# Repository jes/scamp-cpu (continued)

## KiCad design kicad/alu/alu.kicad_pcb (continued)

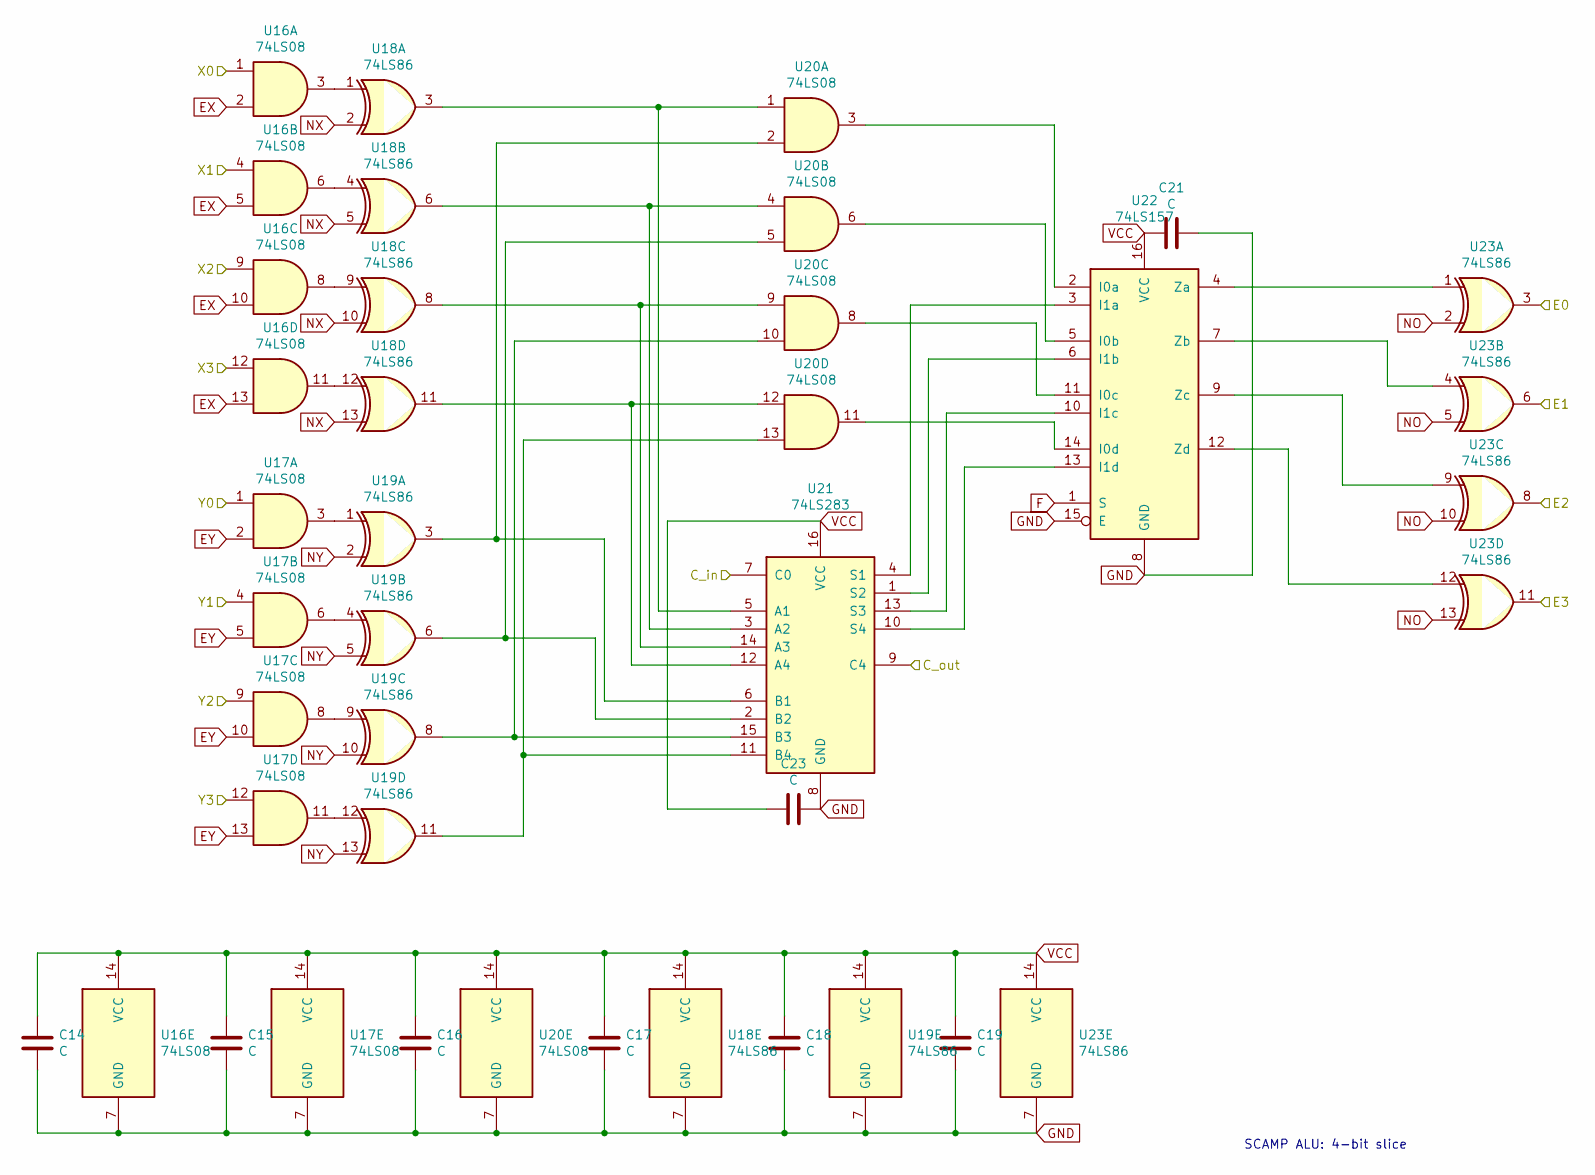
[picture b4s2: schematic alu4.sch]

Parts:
C14, C15, C16, C17, C18, C19, C20, C22: C; C_Disc_D5.0mm_W2.5mm_P2.50mm
U7, U8, U9: 74LS08; DIP-14_W7.62mm_Socket
U11: 74LS283; DIP-16_W7.62mm_Socket
U12: 74LS157; DIP-16_W7.62mm_Socket
U13, U14, U15: 74LS86; DIP-14_W7.62mm_Socket

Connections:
/aluhigh/C_in: U11.9 (C4); also elsewhere on the board
E0: U15.3; also elsewhere on the board
E1: U15.6; also elsewhere on the board
E2: U15.8; also elsewhere on the board
E3: U15.11; also elsewhere on the board
EX: U7.2, U7.5, U7.10, U7.13; also elsewhere on the board
EY: U8.2, U8.5, U8.10, U8.13; also elsewhere on the board
F: U12.1 (S); also elsewhere on the board
GND: C14.2, C15.2, C16.2, C17.2, C18.2, C19.2, C20.1, C22.1, U7.7 (GND), U8.7 (GND), U9.7 (GND), U11.8 (GND), U12.8 (GND), U12.15 (E), U13.7 (GND), U14.7 (GND), U15.7 (GND); also elsewhere on the board
NO: U15.2, U15.5, U15.10, U15.13; also elsewhere on the board
NX: U13.2, U13.5, U13.10, U13.13; also elsewhere on the board
NY: U14.2, U14.5, U14.10, U14.13; also elsewhere on the board
unnamed: U11.1 (S2), U12.6 (I1b)
unnamed: U9.5, U11.2 (B2), U14.6
unnamed: U9.4, U11.3 (A2), U13.6
unnamed: U11.4 (S1), U12.3 (I1a)
unnamed: U9.1, U11.5 (A1), U13.3
unnamed: U9.2, U11.6 (B1), U14.3
unnamed: U11.10 (S4), U12.13 (I1d)
unnamed: U9.13, U11.11 (B4), U14.11
unnamed: U9.12, U11.12 (A4), U13.11
unnamed: U11.13 (S3), U12.10 (I1c)
unnamed: U9.9, U11.14 (A3), U13.8
unnamed: U9.10, U11.15 (B3), U14.8
unnamed: U9.3, U12.2 (I0a)
unnamed: U12.4 (Za), U15.1
unnamed: U9.6, U12.5 (I0b)
unnamed: U12.7 (Zb), U15.4
unnamed: U12.9 (Zc), U15.9
unnamed: U9.8, U12.11 (I0c)
unnamed: U12.12 (Zd), U15.12
unnamed: U9.11, U12.14 (I0d)
unnamed: U7.3, U13.1
unnamed: U7.6, U13.4
unnamed: U7.8, U13.9
unnamed: U7.11, U13.12
unnamed: U8.3, U14.1
unnamed: U8.6, U14.4
unnamed: U8.8, U14.9
unnamed: U8.11, U14.12
VCC: C14.1, C15.1, C16.1, C17.1, C18.1, C19.1, C20.2, C22.2, U7.14 (VCC), U8.14 (VCC), U9.14 (VCC), U11.16 (VCC), U12.16 (VCC), U13.14 (VCC), U14.14 (VCC), U15.14 (VCC); also elsewhere on the board
X0: U7.1; also elsewhere on the board
X1: U7.4; also elsewhere on the board
X2: U7.9; also elsewhere on the board
X3: U7.12; also elsewhere on the board
Y0: U8.1; also elsewhere on the board
Y1: U8.4; also elsewhere on the board
Y2: U8.9; also elsewhere on the board
Y3: U8.12; also elsewhere on the board
carry_in: U11.7 (C0); also elsewhere on the board

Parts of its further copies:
C8, C9, C10, C11, C12, C13, C21, C23: C; C_Disc_D5.0mm_W2.5mm_P2.50mm
U18, U19, U23: 74LS86; DIP-14_W7.62mm_Socket
U20: 74LS08; DIP-14_W7.62mm_Socket
U21: 74LS283; DIP-16_W7.62mm_Socket
U22: 74LS157; DIP-16_W7.62mm_Socket

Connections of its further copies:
/aluhigh/C_in: U21.7 (C0); also elsewhere on the board
E4: U23.3; also elsewhere on the board
E5: U23.6; also elsewhere on the board
E6: U23.8; also elsewhere on the board
E7: U23.11; also elsewhere on the board
F: U22.1 (S); also elsewhere on the board
GND: C8.2, C9.2, C10.2, C11.2, C12.2, C13.2, C21.1, C23.1, U18.7 (GND), U19.7 (GND), U20.7 (GND), U21.8 (GND), U22.8 (GND), U22.15 (E), U23.7 (GND); also elsewhere on the board
NO: U23.2, U23.5, U23.10, U23.13; also elsewhere on the board
NX: U18.2, U18.5, U18.10, U18.13; also elsewhere on the board
NY: U19.2, U19.5, U19.10, U19.13; also elsewhere on the board
unnamed 144: U18.1; also elsewhere on the board
unnamed 145: U18.4; also elsewhere on the board
unnamed 146: U18.9; also elsewhere on the board
unnamed 147: U18.12; also elsewhere on the board
unnamed 148: U19.1; also elsewhere on the board
unnamed 149: U19.4; also elsewhere on the board
unnamed 150: U19.9; also elsewhere on the board
unnamed 151: U19.12; also elsewhere on the board
unnamed: U18.3, U20.1, U21.5 (A1)
unnamed: U18.6, U20.4, U21.3 (A2)
unnamed: U18.8, U20.9, U21.14 (A3)
unnamed: U18.11, U20.12, U21.12 (A4)
unnamed: U19.3, U20.2, U21.6 (B1)
unnamed: U19.6, U20.5, U21.2 (B2)
unnamed: U19.8, U20.10, U21.15 (B3)
unnamed: U19.11, U20.13, U21.11 (B4)
unnamed: U20.3, U22.2 (I0a)
unnamed: U20.6, U22.5 (I0b)
unnamed: U20.8, U22.11 (I0c)
unnamed: U20.11, U22.14 (I0d)
unnamed: U21.1 (S2), U22.6 (I1b)
unnamed: U21.4 (S1), U22.3 (I1a)
unnamed: U21.10 (S4), U22.13 (I1d)
unnamed: U21.13 (S3), U22.10 (I1c)
unnamed: U22.4 (Za), U23.1
unnamed: U22.7 (Zb), U23.4
unnamed: U22.9 (Zc), U23.9
unnamed: U22.12 (Zd), U23.12
VCC: C8.1, C9.1, C10.1, C11.1, C12.1, C13.1, C21.2, C23.2, U18.14 (VCC), U19.14 (VCC), U20.14 (VCC), U21.16 (VCC), U22.16 (VCC), U23.14 (VCC); also elsewhere on the board
carry_out: U21.9 (C4); also elsewhere on the board

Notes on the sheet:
SCAMP ALU: 4-bit slice

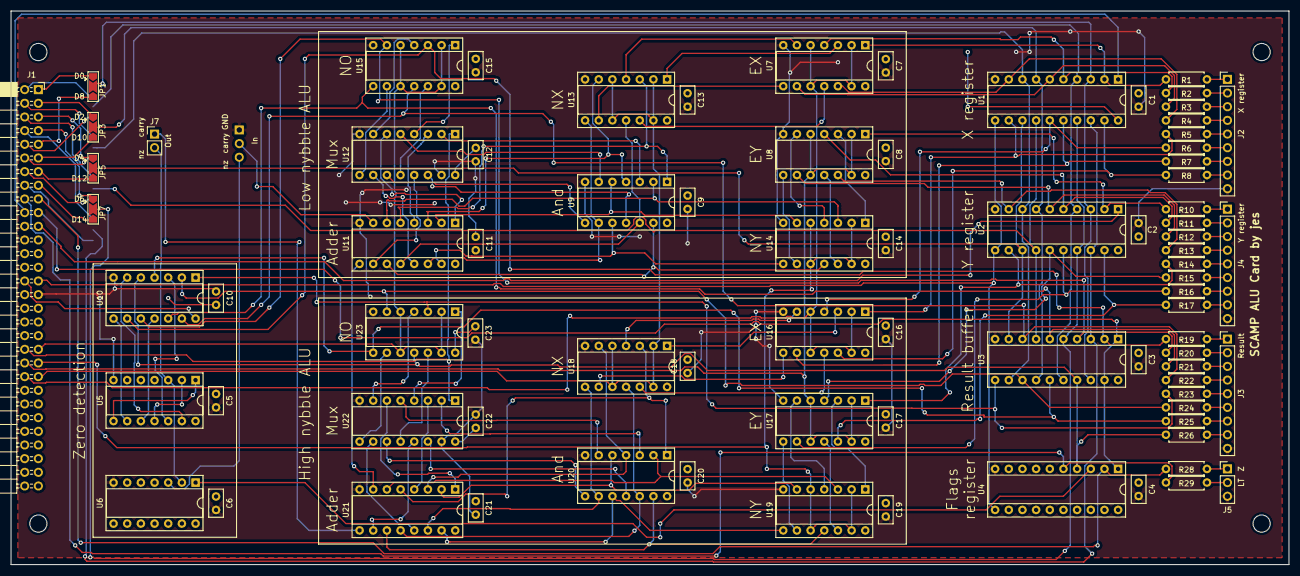
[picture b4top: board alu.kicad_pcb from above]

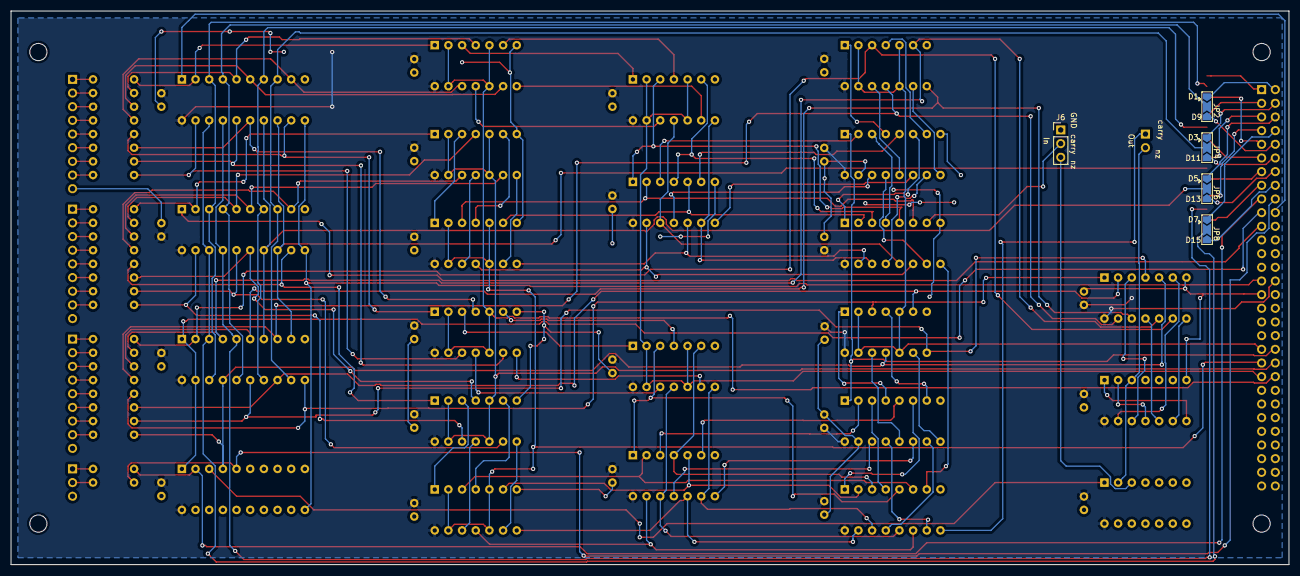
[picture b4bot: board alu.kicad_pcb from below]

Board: 2 copper layers, 237.5 x 102.9 mm, 87 parts (5 on the bottom side), 156 nets.

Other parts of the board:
U16, U17: 74LS08; DIP-14_W7.62mm_Socket

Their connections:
EX: U16.2, U16.5, U16.10, U16.13; also elsewhere on the board
EY: U17.2, U17.5, U17.10, U17.13; also elsewhere on the board
GND: U16.7, U17.7; also elsewhere on the board
unnamed 144: U16.3; also elsewhere on the board
unnamed 145: U16.6; also elsewhere on the board
unnamed 146: U16.8; also elsewhere on the board
unnamed 147: U16.11; also elsewhere on the board
unnamed 148: U17.3; also elsewhere on the board
unnamed 149: U17.6; also elsewhere on the board
unnamed 150: U17.8; also elsewhere on the board
unnamed 151: U17.11; also elsewhere on the board
VCC: U16.14, U17.14; also elsewhere on the board
X4: U16.1; also elsewhere on the board
X5: U16.4; also elsewhere on the board
X6: U16.9; also elsewhere on the board
X7: U16.12; also elsewhere on the board
Y4: U17.1; also elsewhere on the board
Y5: U17.4; also elsewhere on the board
Y6: U17.9; also elsewhere on the board
Y7: U17.12; also elsewhere on the board

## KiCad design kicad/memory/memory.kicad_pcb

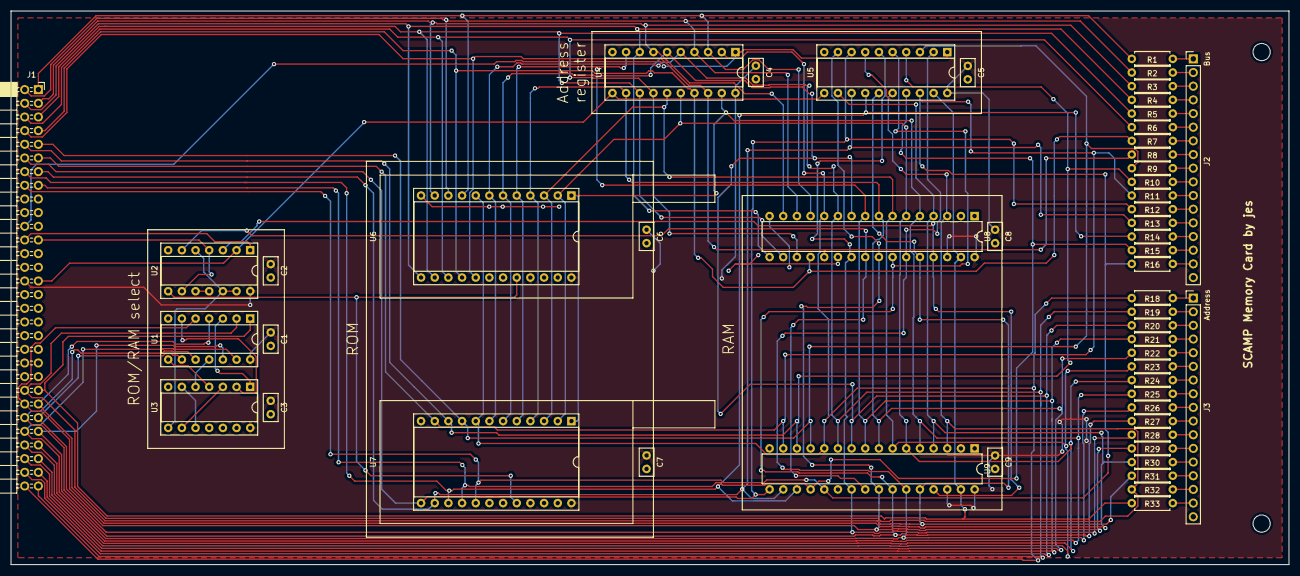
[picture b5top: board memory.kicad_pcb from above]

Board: 2 copper layers, 237.5 x 102.9 mm, 53 parts (0 on the bottom side), 81 nets.

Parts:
C1, C2, C3, C4, C5, C6, C7, C8, C9: C; C_Disc_D5.0mm_W2.5mm_P2.50mm
J1: Conn_02x30_Counter_Clockwise; PinSocket_2x30_P2.54mm_Horizontal
J2, J3: Conn_01x17_Male; PinHeader_1x17_P2.54mm_Vertical
R1, R2, R3, R4, R5, R6, R7, R8, R9, R10, R11, R12, R13, R14, R15, R16, R18, R19, R20, R21, R22, R23, R24, R25, R26, R27, R28, R29, R30, R31, R32, R33: R; R_Axial_DIN0207_L6.3mm_D2.5mm_P7.62mm_Horizontal
U1, U3: 74LS32; DIP-14_W7.62mm_Socket
U2: 74LS00; DIP-14_W7.62mm_Socket
U4, U5: 74LS377; DIP-20_W7.62mm_Socket
U6, U7: 28C16; DIP-24_W15.24mm_Socket
U8, U9: W24512A; DIP-32_W7.62mm

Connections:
A0: J1.60, R18.1, U4.2, U6.8, U7.8, U8.12, U9.12
A1: J1.59, R19.1, U4.5, U6.7, U7.7, U8.11, U9.11
A2: J1.58, R20.1, U4.6, U6.6, U7.6, U8.10, U9.10
A3: J1.57, R21.1, U4.9, U6.5, U7.5, U8.9, U9.9
A4: J1.56, R22.1, U4.12, U6.4, U7.4, U8.8, U9.8
A5: J1.55, R23.1, U4.15, U6.3, U7.3, U8.7, U9.7
A6: J1.54, R24.1, U4.16, U6.2, U7.2, U8.6, U9.6
A7: J1.53, R25.1, U4.19, U6.1, U7.1, U8.5, U9.5
A8: J1.52, R26.1, U1.13, U5.2, U8.27, U9.27
A9: J1.51, R27.1, U1.12, U5.5, U8.26, U9.26
A10: J1.50, R28.1, U1.10, U5.6, U8.23, U9.23
A11: J1.49, R29.1, U1.9, U5.9, U8.25, U9.25
A12: J1.48, R30.1, U1.5, U5.12, U8.4, U9.4
A13: J1.47, R31.1, U1.4, U5.15, U8.28, U9.28
A14: J1.46, R32.1, U1.2, U5.16, U8.3, U9.3
A15: J1.45, R33.1, U1.1, U5.19, U8.31, U9.31
CLK: J1.29, U2.2, U4.11, U5.11
D0: J1.1, R1.1, U4.3, U6.9, U8.13
D1: J1.2, R2.1, U4.4, U6.10, U8.14
D2: J1.3, R3.1, U4.7, U6.11, U8.15
D3: J1.4, R4.1, U4.8, U6.13, U8.17
D4: J1.5, R5.1, U4.13, U6.14, U8.18
D5: J1.6, R6.1, U4.14, U6.15, U8.19
D6: J1.7, R7.1, U4.17, U6.16, U8.20
D7: J1.8, R8.1, U4.18, U6.17, U8.21
D8: J1.9, R9.1, U5.3, U7.9, U9.13
D9: J1.10, R10.1, U5.4, U7.10, U9.14
D10: J1.11, R11.1, U5.7, U7.11, U9.15
D11: J1.12, R12.1, U5.8, U7.13, U9.17
D12: J1.13, R13.1, U5.13, U7.14, U9.18
D13: J1.14, R14.1, U5.14, U7.15, U9.19
D14: J1.15, R15.1, U5.17, U7.16, U9.20
D15: J1.16, R16.1, U5.18, U7.17, U9.21
GND: C1.2, C2.2, C3.2, C4.2, C5.2, C6.2, C7.2, C8.2, C9.2, J1.31, J2.17, J3.17, U1.7, U2.7, U3.7, U4.10, U5.10, U6.12, U6.18, U6.19, U6.22, U6.23, U7.12, U7.18, U7.19, U7.22, U7.23, U8.16, U8.22, U9.16, U9.22
MI: J1.24, U2.1
MO: J1.23, U2.4, U2.9
unnamed: J2.1, R1.2
unnamed: J2.2, R2.2
unnamed: J2.3, R3.2
unnamed: J2.4, R4.2
unnamed: J2.5, R5.2
unnamed: J2.6, R6.2
unnamed: J2.7, R7.2
unnamed: J2.8, R8.2
unnamed: J2.9, R9.2
unnamed: J2.10, R10.2
unnamed: J2.11, R11.2
unnamed: J2.12, R12.2
unnamed: J2.13, R13.2
unnamed: J2.14, R14.2
unnamed: J2.15, R15.2
unnamed: J2.16, R16.2
unnamed: J3.1, R18.2
unnamed: J3.2, R19.2
unnamed: J3.3, R20.2
unnamed: J3.4, R21.2
unnamed: J3.5, R22.2
unnamed: J3.6, R23.2
unnamed: J3.7, R24.2
unnamed: J3.8, R25.2
unnamed: J3.9, R26.2
unnamed: J3.10, R27.2
unnamed: J3.11, R28.2
unnamed: J3.12, R29.2
unnamed: J3.13, R30.2
unnamed: J3.14, R31.2
unnamed: J3.15, R32.2
unnamed: J3.16, R33.2
unnamed: U1.3, U3.1
unnamed: U1.6, U3.2
unnamed: U1.8, U3.4
unnamed: U1.11, U3.5
unnamed: U2.10, U2.11
unnamed: U3.3, U3.9
unnamed: U3.6, U3.10
VCC: C1.1, C2.1, C3.1, C4.1, C5.1, C6.1, C7.1, C8.1, C9.1, J1.30, U1.14, U2.14, U3.14, U4.20, U5.20, U6.21, U6.24, U7.21, U7.24, U8.30, U8.32, U9.30, U9.32
want_ram: U2.5, U2.12, U2.13, U3.8
~AI~: J1.22, U4.1, U5.1
~LOAD_CLK~: U2.3, U8.29, U9.29
~RAM_EN~: U2.6, U8.24, U9.24
~ROM_EN~: U2.8, U6.20, U7.20

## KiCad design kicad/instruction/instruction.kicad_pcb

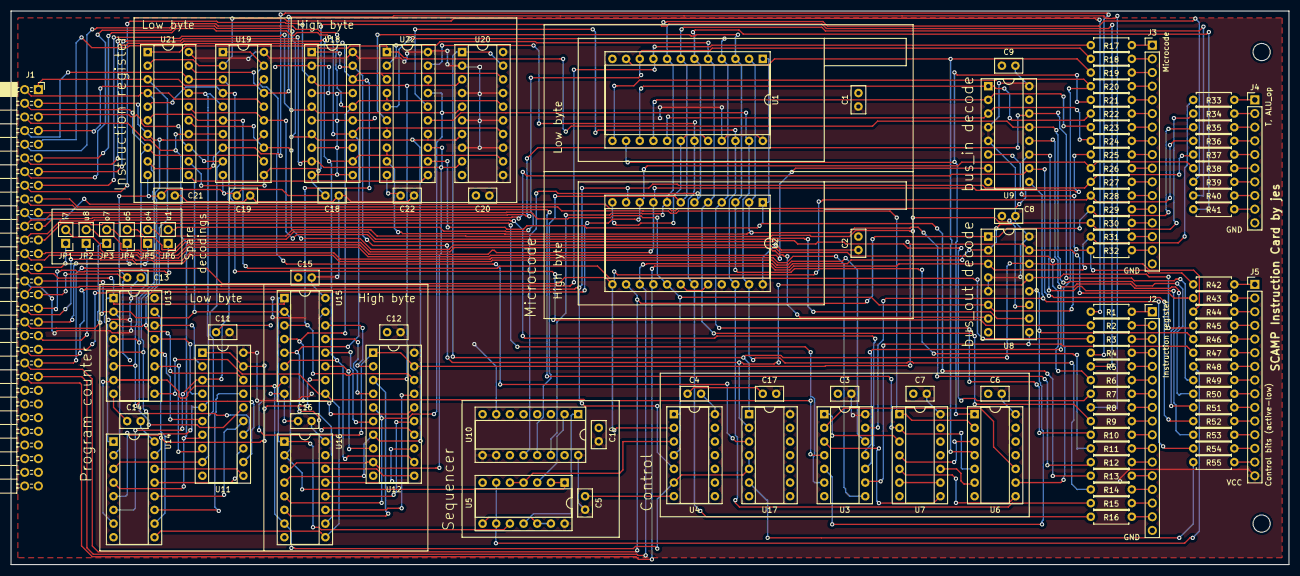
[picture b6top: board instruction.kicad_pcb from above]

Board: 2 copper layers, 237.5 x 102.9 mm, 110 parts (0 on the bottom side), 172 nets.

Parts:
C1, C2, C3, C4, C5, C6, C7, C8, C9, C10, C11, C12, C13, C14, C15, C16, C17, C18, C19, C20, C21, C22: C; C_Disc_D5.0mm_W2.5mm_P2.50mm
J1: Conn_02x30_Counter_Clockwise; PinSocket_2x30_P2.54mm_Horizontal
J2, J3: Conn_01x17_Male; PinHeader_1x17_P2.54mm_Vertical
J4: Conn_01x10_Male; PinHeader_1x10_P2.54mm_Vertical
J5: Conn_01x15_Male; PinHeader_1x15_P2.54mm_Vertical
JP1, JP2, JP3, JP4, JP5, JP6: Jumper_NO_Small; PinHeader_1x02_P2.54mm_Vertical
R1, R2, R3, R4, R5, R6, R7, R8, R9, R10, R11, R12, R13, R14, R15, R16, R17, R18, R19, R20, R21, R22, R23, R24, R25, R26, R27, R28, R29, R30, R31, R32, R33, R34, R35, R36, R37, R38, R39, R40, R41, R42, R43, R44, R45, R46, R47, R48, R49, R50, R51, R52, R53, R54, R55: R; R_Axial_DIN0207_L6.3mm_D2.5mm_P7.62mm_Horizontal
U1, U2: 28C16; DIP-24_W15.24mm_Socket
U3: 74LS04; DIP-14_W7.62mm_Socket
U4, U6: 74LS08; DIP-14_W7.62mm_Socket
U5, U17: 74LS00; DIP-14_W7.62mm_Socket
U7: 74LS32; DIP-14_W7.62mm_Socket
U8, U9: 74LS138; DIP-16_W7.62mm_Socket
U10, U13, U14, U15, U16: 74LS161; DIP-16_W7.62mm_Socket
U11, U12, U18, U19, U20: 74LS244; DIP-20_W7.62mm_Socket
U21, U22: 74LS377; DIP-20_W7.62mm_Socket

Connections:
CLK: J1.29, U5.1, U5.2, U13.2, U14.2, U15.2, U16.2, U21.11, U22.11
D0: J1.1, U11.18, U13.3, U19.18, U21.3
D1: J1.2, U11.16, U13.4, U19.16, U21.4
D2: J1.3, U11.14, U13.5, U19.14, U21.7
D3: J1.4, U11.12, U13.6, U19.12, U21.8
D4: J1.5, U11.9, U14.3, U19.9, U21.13
D5: J1.6, U11.7, U14.4, U19.7, U21.14
D6: J1.7, U11.5, U14.5, U19.5, U21.17
D7: J1.8, U11.3, U14.6, U19.3, U21.18
D8: J1.9, U12.18, U15.3, U18.18, U20.18, U22.3
D9: J1.10, U12.16, U15.4, U18.16, U20.16, U22.4
D10: J1.11, U12.14, U15.5, U18.14, U20.14, U22.7
D11: J1.12, U12.12, U15.6, U18.12, U20.12, U22.8
D12: J1.13, U12.9, U16.3, U18.9, U20.9, U22.13
D13: J1.14, U12.7, U16.4, U18.7, U20.7, U22.14
D14: J1.15, U12.5, U16.5, U18.5, U20.5, U22.17
D15: J1.16, U12.3, U16.6, U18.3, U20.3, U22.18
DI: J1.26, U3.12
DO: J1.25, U3.8
EX: J1.44, R31.1, R33.1, U2.16, U8.3
EY: J1.42, R29.1, R35.1, U2.14, U8.1
F: J1.40, R27.1, R37.1, U2.11, U4.5
GND: C1.2, C2.2, C3.2, C4.2, C5.2, C6.2, C7.2, C8.2, C9.2, C10.2, C11.2, C12.2, C13.2, C14.2, C15.2, C16.2, C17.2, C18.2, C19.2, C20.2, C21.2, C22.2, J1.31, J2.17, J3.17, J4.10, U1.12, U1.18, U1.20, U2.12, U2.18, U2.20, U3.7, U4.7, U5.7, U6.7, U7.7, U8.8, U9.8, U10.8, U11.10, U12.10, U13.8, U14.8, U15.8, U16.8, U17.7, U18.2, U18.4, U18.6, U18.8, U18.10, U18.11, U18.13, U18.15, U18.17, U19.10, U20.10, U21.10, U22.10
GT: U3.2, U6.10
I0: R1.1, U19.2, U21.2
I1: R2.1, U19.4, U21.5
I2: R3.1, U19.6, U21.6
I3: R4.1, U19.8, U21.9
I4: R5.1, U19.11, U21.12
I5: R6.1, U19.13, U21.15
I6: R7.1, U19.15, U21.16
I7: R8.1, U19.17, U21.19
I8: R9.1, U1.5, U2.5, U22.2
I9: R10.1, U1.4, U2.4, U22.5
I10: R11.1, U1.3, U2.3, U22.6
I11: R12.1, U1.2, U2.2, U22.9
I12: R13.1, U1.1, U2.1, U22.12
I13: R14.1, U1.23, U2.23, U22.15
I14: R15.1, U1.22, U2.22, U22.16
I15: R16.1, U1.19, U2.19, U22.19
JGT: R20.1, U1.13, U6.9
JGT_GT: U6.8, U7.5
JLT: R19.1, U1.11, U6.4
JLT_LT: U6.6, U7.10
JMP: U3.3, U7.8
JZ: R21.1, U1.14, U6.1
JZ_Z: U6.3, U7.4
LT: J1.18, U6.5, U7.2
MI: J1.24, U3.10
MO: J1.23, U3.6
NO: J1.39, R26.1, R38.1, U2.10
NX: J1.43, R30.1, R34.1, U2.15, U8.2
NY: J1.41, R28.1, R36.1, U2.13, U4.2
unnamed: J1.27, JP1.1
unnamed: J1.33, JP6.1
unnamed: J1.34, JP5.1
unnamed: J1.35, JP4.1
unnamed: J1.36, JP3.1
unnamed: J1.37, JP2.1
unnamed: J2.1, R1.2
unnamed: J2.2, R2.2
unnamed: J2.3, R3.2
unnamed: J2.4, R4.2
unnamed: J2.5, R5.2
unnamed: J2.6, R6.2
unnamed: J2.7, R7.2
unnamed: J2.8, R8.2
unnamed: J2.9, R9.2
unnamed: J2.10, R10.2
unnamed: J2.11, R11.2
unnamed: J2.12, R12.2
unnamed: J2.13, R13.2
unnamed: J2.14, R14.2
unnamed: J2.15, R15.2
unnamed: J2.16, R16.2
unnamed: J3.1, R17.2
unnamed: J3.2, R18.2
unnamed: J3.3, R19.2
unnamed: J3.4, R20.2
unnamed: J3.5, R21.2
unnamed: J3.6, R22.2
unnamed: J3.7, R23.2
unnamed: J3.8, R24.2
unnamed: J3.9, R25.2
unnamed: J3.10, R26.2
unnamed: J3.11, R27.2
unnamed: J3.12, R28.2
unnamed: J3.13, R29.2
unnamed: J3.14, R30.2
unnamed: J3.15, R31.2
unnamed: J3.16, R32.2
unnamed: J4.1, R33.2
unnamed: J4.2, R34.2
unnamed: J4.3, R35.2
unnamed: J4.4, R36.2
unnamed: J4.5, R37.2
unnamed: J4.6, R38.2
unnamed: J4.7, R39.2
unnamed: J4.8, R40.2
unnamed: J4.9, R41.2
unnamed: J5.1, R42.2
unnamed: J5.2, R43.2
unnamed: J5.3, R44.2
unnamed: J5.4, R45.2
unnamed: J5.5, R46.2
unnamed: J5.6, R47.2
unnamed: J5.7, R48.2
unnamed: J5.8, R49.2
unnamed: J5.9, R50.2
unnamed: J5.10, R51.2
unnamed: J5.11, R52.2
unnamed: J5.12, R53.2
unnamed: J5.13, R54.2
unnamed: J5.14, R55.2
unnamed: U5.8, U5.12, U5.13
unnamed: U7.6, U7.9
unnamed: U13.15, U14.10
unnamed: U14.15, U15.10
unnamed: U15.15, U16.10
P0: U11.2, U13.14
P1: U11.4, U13.13
P2: U11.6, U13.12
P3: U11.8, U13.11
P4: U11.11, U14.14
P5: U11.13, U14.13
P6: U11.15, U14.12
P7: U11.17, U14.11
P8: U12.2, U15.14
P9: U12.4, U15.13
P10: U12.6, U15.12
P11: U12.8, U15.11
P12: U12.11, U16.14
P13: U12.13, U16.13
P14: U12.15, U16.12
P15: U12.17, U16.11
PP: U4.6, U13.7, U13.10, U14.7, U15.7, U16.7, U17.4, U17.5
RT: U4.3, U5.4, U5.5
T0: R39.1, U1.8, U2.8, U10.14
T1: R40.1, U1.7, U2.7, U10.13
T2: R41.1, U1.6, U2.6, U10.12
U0: J1.32, R17.1, U1.9
U1: JP6.2, R18.1, U1.10
U5: R22.1, U1.15, U9.1
U6: R23.1, U1.16, U9.2
U7: R24.1, U1.17, U9.3
U8: JP2.2, R25.1, U2.9
U15: J1.19, R32.1, R42.1, U2.17, U4.1, U4.4, U8.6, U9.6
VCC: C1.1, C2.1, C3.1, C4.1, C5.1, C6.1, C7.1, C8.1, C9.1, C10.1, C11.1, C12.1, C13.1, C14.1, C15.1, C16.1, C17.1, C18.1, C19.1, C20.1, C21.1, C22.1, J1.30, J5.15, U1.21, U1.24, U2.21, U2.24, U3.14, U4.14, U5.14, U6.14, U7.14, U8.4, U8.5, U8.16, U9.4, U9.5, U9.16, U10.7, U10.9, U10.10, U10.16, U11.20, U12.20, U13.16, U14.16, U15.16, U16.16, U17.14, U18.20, U19.20, U20.2, U20.4, U20.6, U20.8, U20.11, U20.13, U20.15, U20.17, U20.20, U21.20, U22.20
Z: J1.17, U6.2, U7.1
Z_LT: U3.1, U7.3
inv_CLK: U5.3, U10.2
inv_DI: R54.1, U3.13, U9.9
inv_DO: R47.1, U3.9, U8.9
inv_MI: R53.1, U3.11, U9.12
inv_MO: R46.1, U3.5, U8.12
inv_PP: R55.1, U17.6
inv_RT: R48.1, U5.6, U5.9
spare_I7: JP1.2, U9.7
spare_O4: JP5.2, U8.11
spare_O5: JP4.2, U8.10
spare_O7: JP3.2, U8.7
~AI~: J1.22, R49.1, U9.14
~II~: R50.1, U9.13, U21.1, U22.1
~IOH~: R44.1, U8.14, U17.1, U20.1, U20.19
~IOLH~: U17.3, U19.1, U19.19
~IOL~: R45.1, U8.13, U17.2, U18.1, U18.19
~JMP~: U3.4, U13.9, U14.9, U15.9, U16.9
~PO~: R43.1, U8.15, U11.1, U11.19, U12.1, U12.19
~RESET~: J1.28, U5.10, U13.1, U14.1, U15.1, U16.1
~XI~: J1.20, R51.1, U9.11
~YI~: J1.21, R52.1, U9.10
~reset_T~: U5.11, U10.1

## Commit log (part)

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2021-11-20 Add SER_LONGREAD flag
2021-11-20 serial: make use of LONGREAD flag, and delayed packet ACK, to improve throughput
2021-11-20 Revert "aocproxy: recover from unexpected response, and run slow enough for real hardware"
    This reverts commit 062cfcdbba21daf2abf59ec83e97bf648681db07.
2021-11-20 Revert "Update serial protocol to support checksums and synchronisation"
    This reverts commit d104ef9712ae535607cd63ff953dd1113420b1ce.
2021-11-20 Add more serial protocol documentation
2021-11-20 aoc: buffer in memory instead of writing to stdout
2021-11-20 aoc: show content on stderr while buffering
2021-11-22 kilo: show 'finding ...' while finding
2021-11-22 glob: don't let '*' match a leading '.'
2021-11-22 Add ps
2021-11-22 ps: close fd after reading
2021-11-22 slc: don't check args[1] if args[0] isn't set
2021-11-22 aoc: don't print uninitialised strings for empty data
2021-11-22 peepopt: optimise another 'ld x, foo; call x' case
2021-11-22 Mention that work has started on 'const' supported
2021-11-26 serial: only enable cooked mode by default for the console, not all devices
2021-11-26 SCAMP::Serial: make clearer when it's ready
2021-11-26 Increase serial transfer speed by 10% (any more becomes unreliable)
2021-11-28 ser: buffer in memory
2021-11-29 kernel: don't crash when restoring a large program into memory
    The problem was that in the event that you ask read() for more than 254 words,
    and the current pointer is at the start of a block on disk, read() will ask cf_blkread()
    to read directly into the user buffer, rather than memcpy()ing to it.
    The problem is that if the program we're restoring is very large, this can lead to
    cf_blkread() putting 254 words into memory, even when the remaining words in the file
    is lower than that, which overwrites some of the kernel causing a crash.
2021-12-01 atoi: move to asm, 2x faster
2021-12-01 install: sudo
2021-12-01 Unlicense
2021-12-02 Link to James Sharman
2021-12-03 aoc: don't show output twice on 'submit'
2021-12-03 Add assert()
2021-12-03 wc: accept a filename on the command line
2021-12-03 Put a trailing newline on submission results
2021-12-03 kilo: make paging behaviour more useful
2021-12-03 Remove unused files from compiler/
2021-12-05 slangc: don't warn about locals overriding globals
2021-12-06 kilo: increase horizontal scroll step size
2021-12-06 init: clear out /tmp,/proc, and save context switching to cat
2021-12-06 Add link to Advent of Code solutions
2021-12-06 Add new picture of computer
2021-12-06 kilo: don't scroll the top line off the help page
2021-12-06 Plan to support more fds
2021-12-06 Add swap()
2021-12-06 serial: fix callback function signature
2021-12-06 aocproxy: add way to get only part 2 without re-sending part 1
2021-12-07 sh: make die() non-fatal
2021-12-11 head: use setbuf
2021-12-11 kilo: add >,< shortcuts for indenting with tab
2021-12-13 Set bs=1k on install script
2021-12-15 Add vzmalloc,vfree
2021-12-15 vfree: free the intermediate arrays
2021-12-15 bufio: fix pseudocode
2021-12-15 asm: don't unlink the output of the 1st pass
2021-12-16 init: don't clear out /tmp
2021-12-27 cf: pre-increment instead of post-increment, to save 1 cycle per IO instruction
2021-12-27 memcpy: pre-increment instead of post-increment, to save 2 cycles per word copied
2021-12-27 Document new instructions
2021-12-29 slangc: turn off recursion warnings
2021-12-29 Peephole optimise new y register usage; remove nand and nor instructions
2022-01-04 atoibase: use atoi when base==10
2022-01-04 bputs: into asm
2022-01-04 Minor improvement to AnyChar
2022-01-28 asm: bodge to allow hashes in .str
2022-05-11 Use lt instead of < in utoabase()
2022-06-12 Add savetpa() syscall
2022-06-13 Add missing endline
2022-06-13 bgetc: make it possible to distinguish between a 0xffff character and EOF condition
2022-06-15 Document bug
2022-06-18 Plan to cache compiled binary in rude
2022-06-19 More efficient format for passing bulk externs into slangc
2022-06-19 Use externs list instead of lib.h/lib.s in slc (knocks ~10s off compile times)
2022-06-19 Asm undirent()
2022-06-19 slangc: support passing foot asm on command line
2022-06-19 Prefer puts() over printf()
2022-06-19 fprintf -> fputs
2022-06-19 bprintf->bput[cs]: save ~1s
2022-06-20 write(): save wasting time on memcpy() and blkread()
    I'm not completely sure that the idea of using cf_blkread_head() is
    legit. If this doesn't work on real hardware then that part will need
    to be reverted.
2022-06-20 kernel: don't truncate or unlink proc files, saves lots of time
2022-06-20 Fix ucode for 'ld (x), i16'
    It was actually implementing 'ld ((x)), i16'
2022-06-20 No longer need to writeglobalsfile() in compile()
2022-06-21 asm implementation of htmaybegrow()
2022-06-21 Fix strlen() of empty string
2022-06-21 Slightly better bgetc()
2022-06-21 Slightly better hashstr()
2022-06-21 Fix fd leak
2022-06-21 Add getpid() syscall
2022-06-21 RUDE: Implement kilo()
2022-06-23 exit(0) after running entrypoint
2022-06-23 RUDE: write out initial stack pointer every time
2022-06-23 Store source of defined functions, allow reversion
2022-06-24 rude: don't strdup all the globals with static strings
2022-06-24 Remove malloc spam
2022-06-24 rude: implement list()
2022-06-26 slangc: add 'gullible' mode where externs aren't validated
2022-06-26 rude: set return value for non-function-call statements
2022-06-27 Revert "rude: set return value for non-function-call statements"
    This reverts commit a1a440ccd0cbc6f2ab523a9250f99b07b84c3dda.
    Functions aren't required to leave their return value in x, so calling
    functions written in assembly language might not work, so we'll just
    put it back to how it was.
2022-06-27 rude: save source update even if the code didn't compile
2022-06-27 rude: faster way to launch kilo
2022-06-28 rude: accept arbitrarily-large input files
2022-06-28 rude: interpret assignments
2022-06-28 rude: interpret array indexing
2022-06-29 emulator: add optional memory dumping
2022-06-30 rude: add .list
2022-07-01 Empty filename is non-file
2022-07-03 Skip useless post-inc
2022-07-03 Explain how nextfreeblk is updated
2022-07-04 Move fsck to userspace
2022-07-06 fs_write: set cached block number correctly when allocating new block
2022-07-08 Add some thoughts on Lisp
2022-07-14 Initial lisp implementation
2022-07-14 More type predicates
2022-07-14 lisp: cons/car/cdr, arithmetic
2022-07-14 Check length of arg list for builtins
2022-07-14 Let lisp programs read files
2022-07-15 lisp: malloc a big enough arena to account for odd-numbered pointers
2022-07-15 Support '-' as a single symbol
2022-07-15 Print strings
2022-07-15 lisp: tail-call cond bodies
2022-07-16 Use cons cells for gc stack
2022-07-16 Implement cond and define using continuations (still need to do evlis)
2022-07-16 Use continuations for evlis: EVAL is no longer recursive!
2022-07-16 Simplify EVAL
2022-07-16 Optimise car/cdr
2022-07-16 Remove unnecessary magnitude comparisons
2022-07-16 Remove unnecessary function call layers
2022-07-17 Add set!
2022-07-18 Add bitmap library
2022-07-18 Put bitmap.sl in fs
2022-07-18 Generate more lib docs
2022-07-19 Add quasiquote
2022-07-19 Tidy up lisp section organisation
2022-07-20 Add lisp lib
2022-07-21 Add eval
2022-07-25 Lisp: begin
2022-08-01 Don't print answers when reading from a file
2022-08-01 setcar,setcdr to asm
2022-08-01 bwrite: to asm
2022-08-02 Now have fsck and lisp
2022-08-02 test
2022-08-03 slangc: stop wasting memory on IO buffers (it already uses bufio)
2022-08-03 Start interpreting expressions
2022-08-03 slangi: pre/post inc/decrement
2022-08-04 slangi: function declarations
2022-08-04 slangi: return, array literals
2022-08-04 slangi: initialisers are optional
2022-08-04 slangi: break, continue
2022-08-04 slangi: include
2022-08-04 slangi: do nothing on multiple-include of same file
2022-08-04 hd: fix 'pos' name collision
2022-08-04 slangi: track break/continue properly across function calls and nested loops
2022-08-04 slangi: free local variables when exiting scope
2022-08-04 malloc: fix test of freeing static pointer; remove broken grow-in-place; use memcpy
2022-08-05 slangi: allocate the trailing 0 for array literals
2022-08-05 slangi: stop using grarrs for function arguments
2022-08-05 slangi: lookup variable addresses at parse time instead of runtime
2022-08-05 slangi: simplify eval_function()
2022-08-05 slangi: reduce dynamic allocations
2022-08-05 slangi: lsalloc/lsfree in asm
2022-08-06 slangi: pre-emptively grow globals table (knock 400ms off startup)
2022-08-06 slangi: constant folding
2022-08-06 slangi: don't constant-fold value-of
2022-08-06 slangi: evaluate function arguments left-to-right
2022-08-09 slangi: compile FunctionCallNodes
2022-08-09 slangi: asm EvalConditionalNode
2022-08-09 slangi: EvalIndexAddressOfNode: less grget
2022-08-10 aoc: give final output unsigned
2022-08-10 rename(): stop throwing NOTDIR when renaming ordinary files
2022-08-10 slangi/rude: add bigint by default
2022-09-07 Don't build pdf by default
2022-10-31 Fix emulator when built with zig cc
2022-11-13 Count lines, characters
2022-11-13 Try to sync serial port again (can come up with spurious bytes at the start)
2022-11-13 Optimise division by 16 in bitmap.sl
2022-11-15 kilo: simplify drawrow(), don't sprintf() with no args, don't allow input of control characters
2022-11-19 Show directory in shell prompt
2022-11-19 fs: only sync at end of each block if not already written
2022-11-19 uasm: remove magic number
2022-11-20 Not safe to use TPA space for buffer because the args are still in the TPA
2022-11-25 Insert spaces, not tabs, when indenting rows
2022-11-25 kilo: J: trim leading whitespace, insert 1 space
2022-12-02 aoc: accept 'get2' instead of 'part2'
2022-12-11 asm bigcmp
    With 4-word bigints:
    +120% bigcmp throughput
    +36% bigdiv/bigmod throughput
2022-12-11 bigint: reduce allocations
2022-12-11 bigint: remove spurious assignment
2022-12-11 Add documentation of integer operation performance
2022-12-12 Add bitmap to library blob, interpreter
2023-05-07 Simplify PreOp/PostOp
2023-06-12 Add zero,one instructions
2023-06-25 There is a better serial protocol now
2023-07-30 Eliminate unnecessary push/pop in magnitude comparisons in self-hosting compiler
2023-07-30 Remove extraneous jmp in magnitude comparisons
2023-10-16 Add 'const' as alias for 'var'
2023-10-16 Fix warning for generating '0' from ALU
2023-10-16 Make constants constant
2023-10-16 Generate consts file
2023-11-03 More const
2023-11-03 Let make know how to get lib.list
2023-11-03 Optimise initialisation of globals from constants, in self-hosted compiler
2023-11-03 Some slangi optimisations
2023-11-03 slangi: simplify EvalLocalNode
2023-11-04 Optimise more ld rN, [01]
2023-11-05 No warnings recursion on getblk
2023-11-05 TABSTOP is not used any more
2023-11-05 bigbit: don't let zeroing r0 clobber flags
2023-11-17 Make 'continue' work again
2023-11-17 slangi: let logical or/and short-circuit
2023-11-24 Add test suite
2023-11-25 Check the 3 test outputs independently
2023-11-25 Add test_grep
2023-11-28 Some more slangi JIT optimisations
2023-11-28 Add bitmap test
2023-11-28 Add initial attempt at regex library
2023-11-29 regex: remove debugging prints
2023-11-29 Add regex tests, and sh quoting test
2023-11-29 Add test_basic.sl
2023-11-30 bigint: less runtime allocation
2023-11-30 regex: stop using inline asm (not compatible with slangi)
2023-11-30 Put regex.sl in fs
2023-12-02 More regex features
2023-12-02 regex: add non-capturing grouping
